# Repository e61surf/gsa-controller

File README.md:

# Surf System Controller - or whatever you want to control...

Feel free to make use of the hardware and software designs here for your project. It is ideally suited for robotics, small electric mobility decives, linear actuator control, or basically anything that needs to drive somewhat high-current motors and needs GPS and Bluetooth. The Atmel 32u4 based, high current board design utilizes:
3 ST Micro motor drivers,
1 Lynx GPS Module, and
1 Microchip BLE Module.

It is designed to fit into a Cinch ModeICE enclosure, which is fully waterproof.

The hardware/software design supports up to a 10 wire, 5 volt control cable and is currently utlizing 2 potentiometers, 3 momentary switches, and 3 LED indicators, but the Atmel 32u4 processor pins can be utlized for many different perposes. 

It can drive up to 3 12v motors/actuators.  Or one of the ST Micro chips can be configured as two 12v outputs for lights, horns, etc...

The board is designed to run on 12v power from a marine or automotive alternator, so it'll handle fluctuations and noise typical in rugged applications.

The BLE module and supporting AVR code supports a custom framed serial protocol for control via a mobile app.  See the documents for more info.

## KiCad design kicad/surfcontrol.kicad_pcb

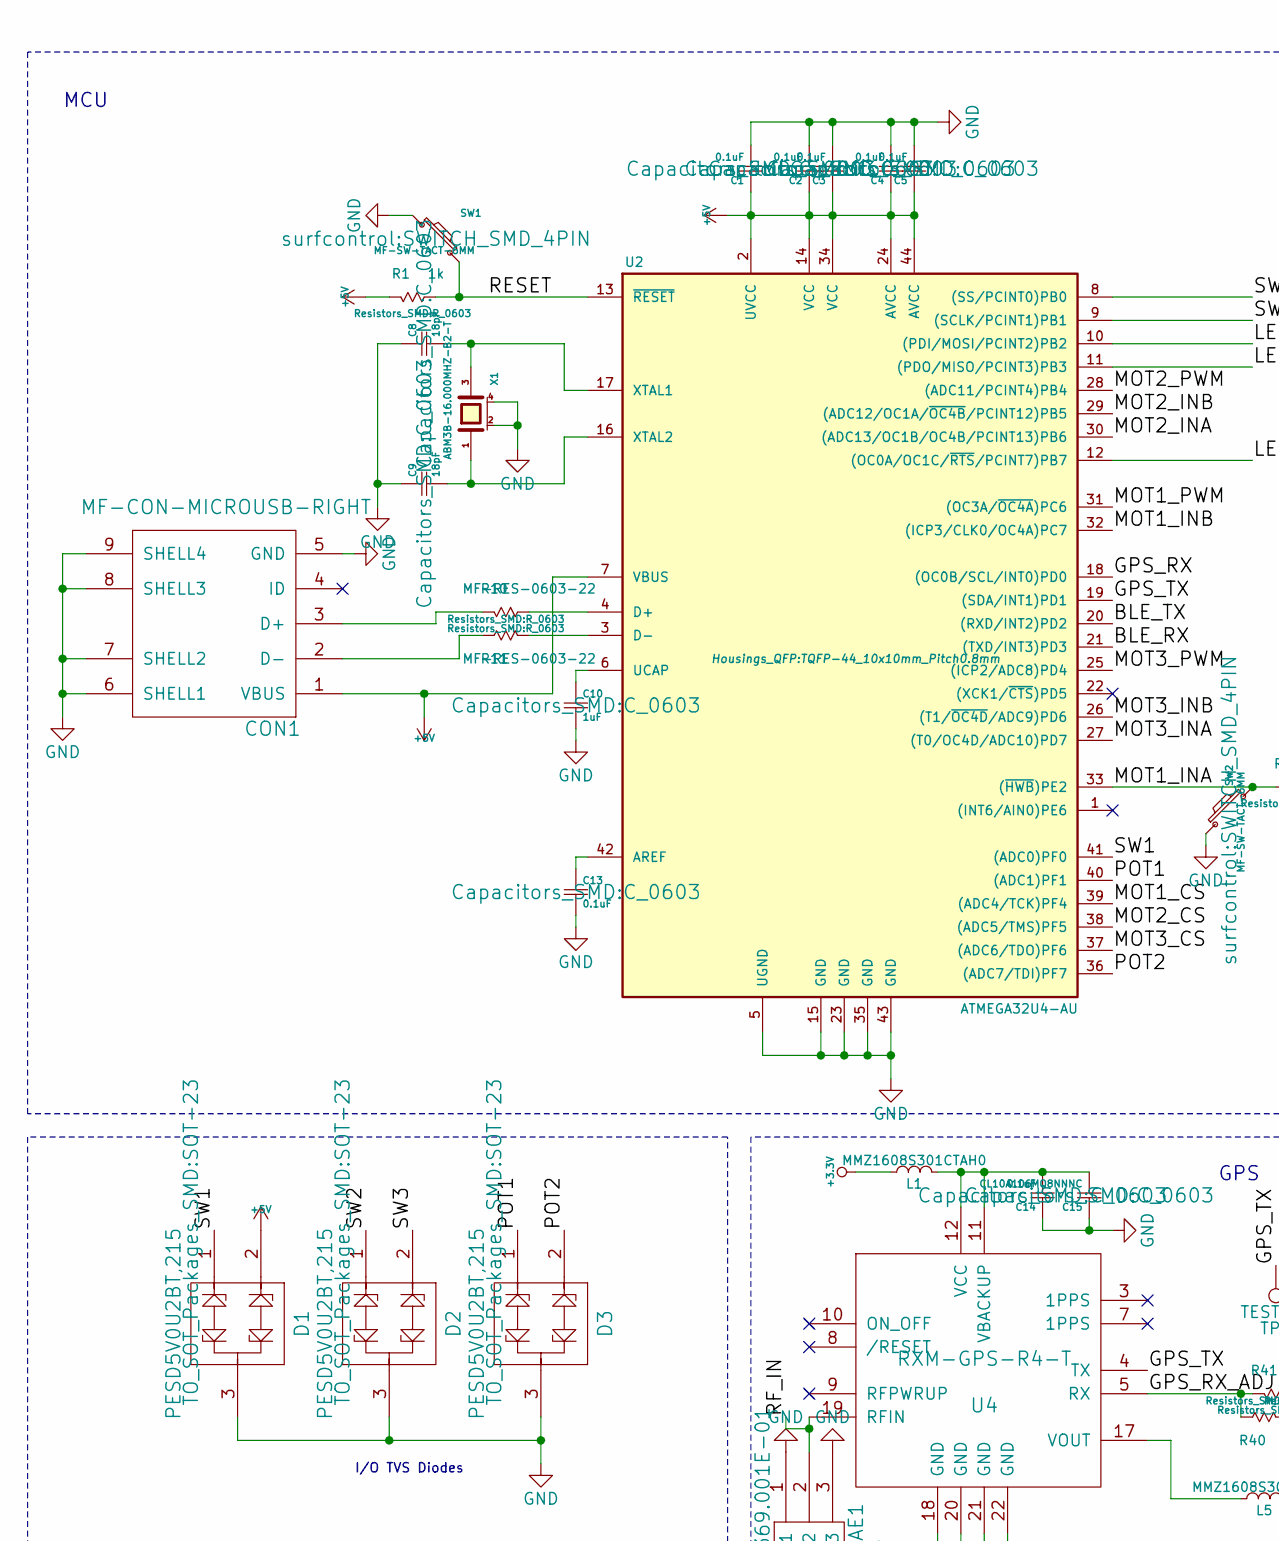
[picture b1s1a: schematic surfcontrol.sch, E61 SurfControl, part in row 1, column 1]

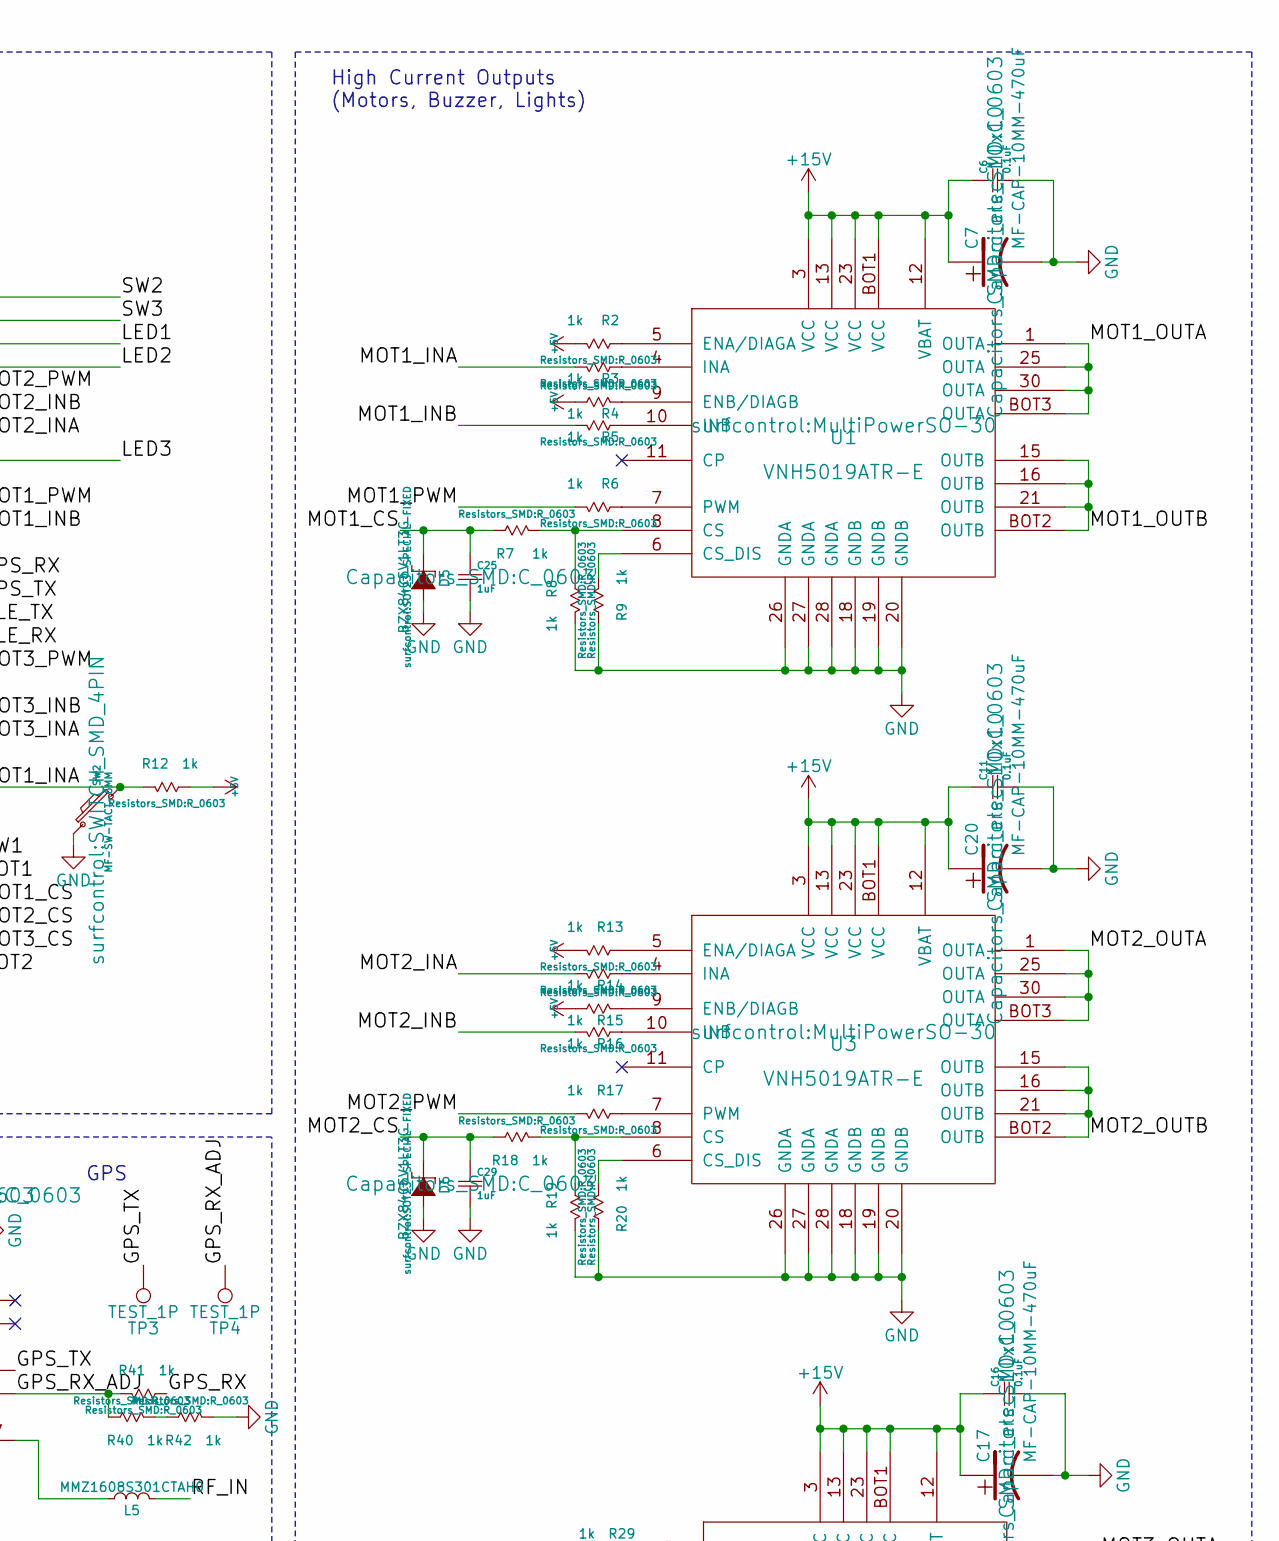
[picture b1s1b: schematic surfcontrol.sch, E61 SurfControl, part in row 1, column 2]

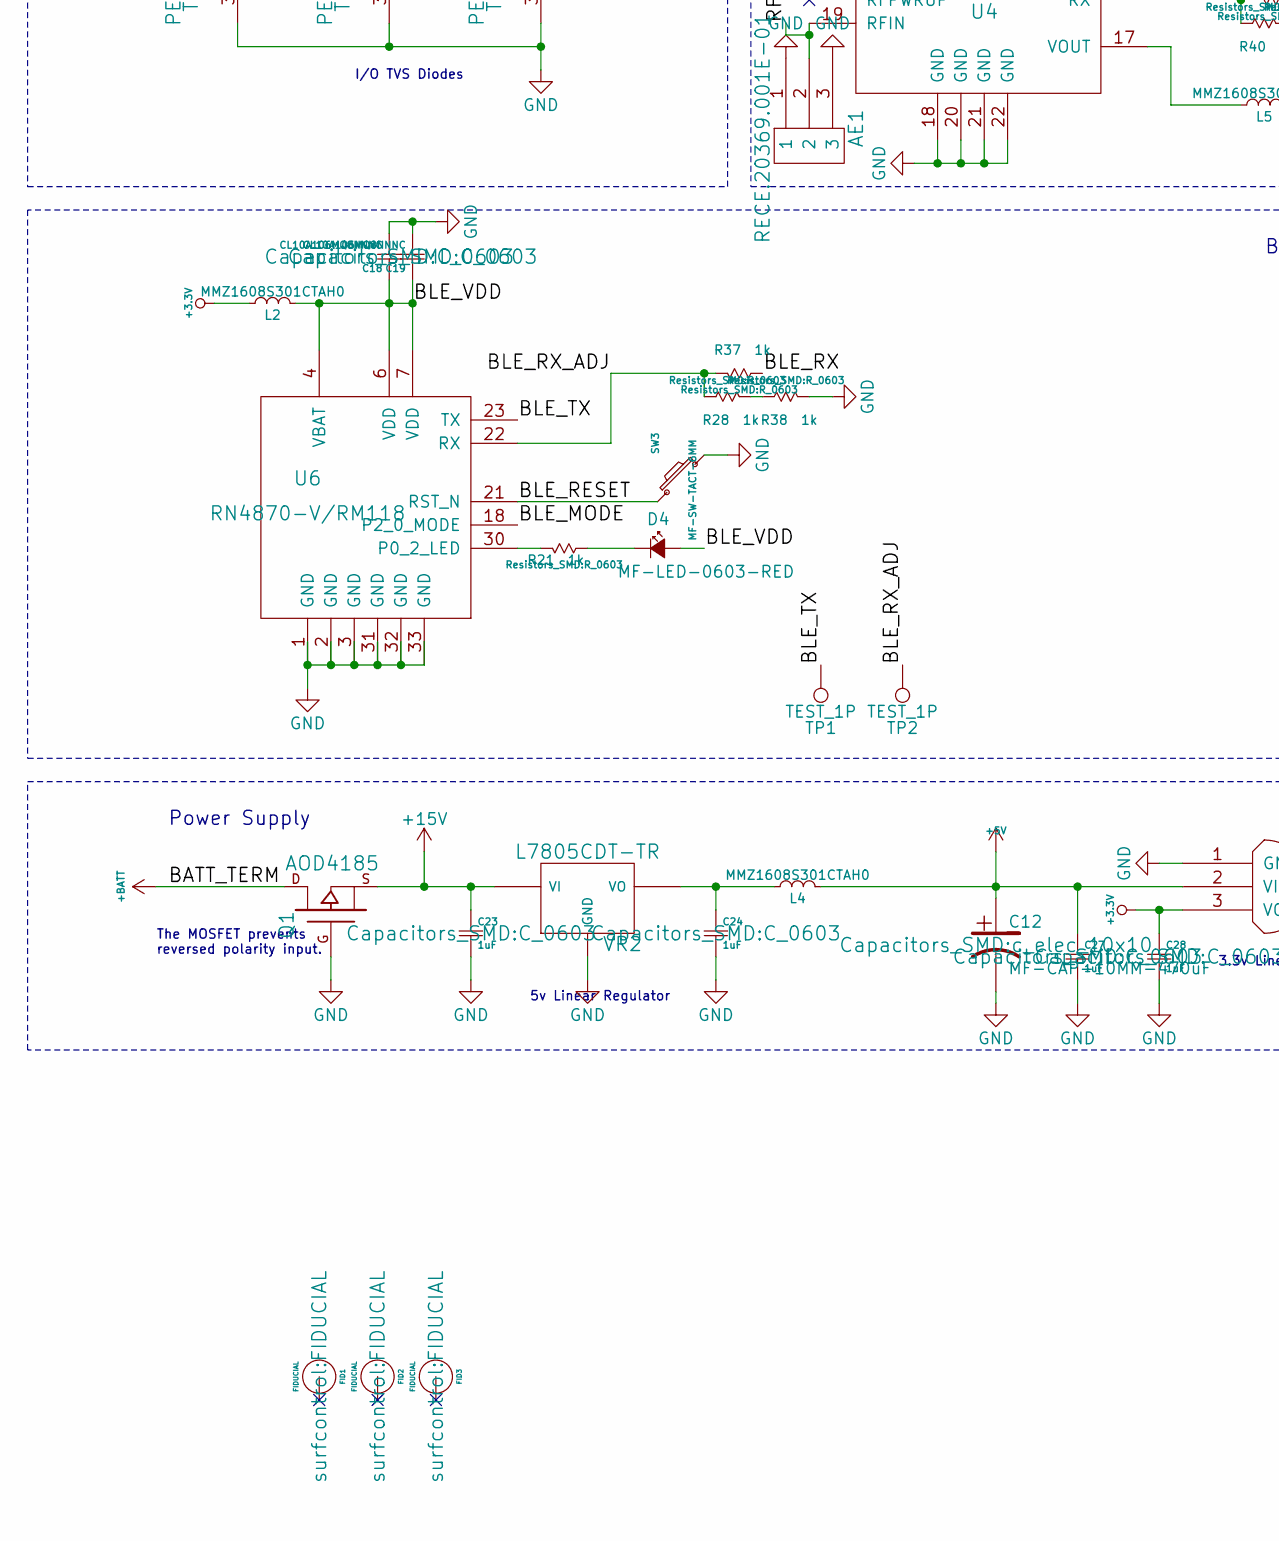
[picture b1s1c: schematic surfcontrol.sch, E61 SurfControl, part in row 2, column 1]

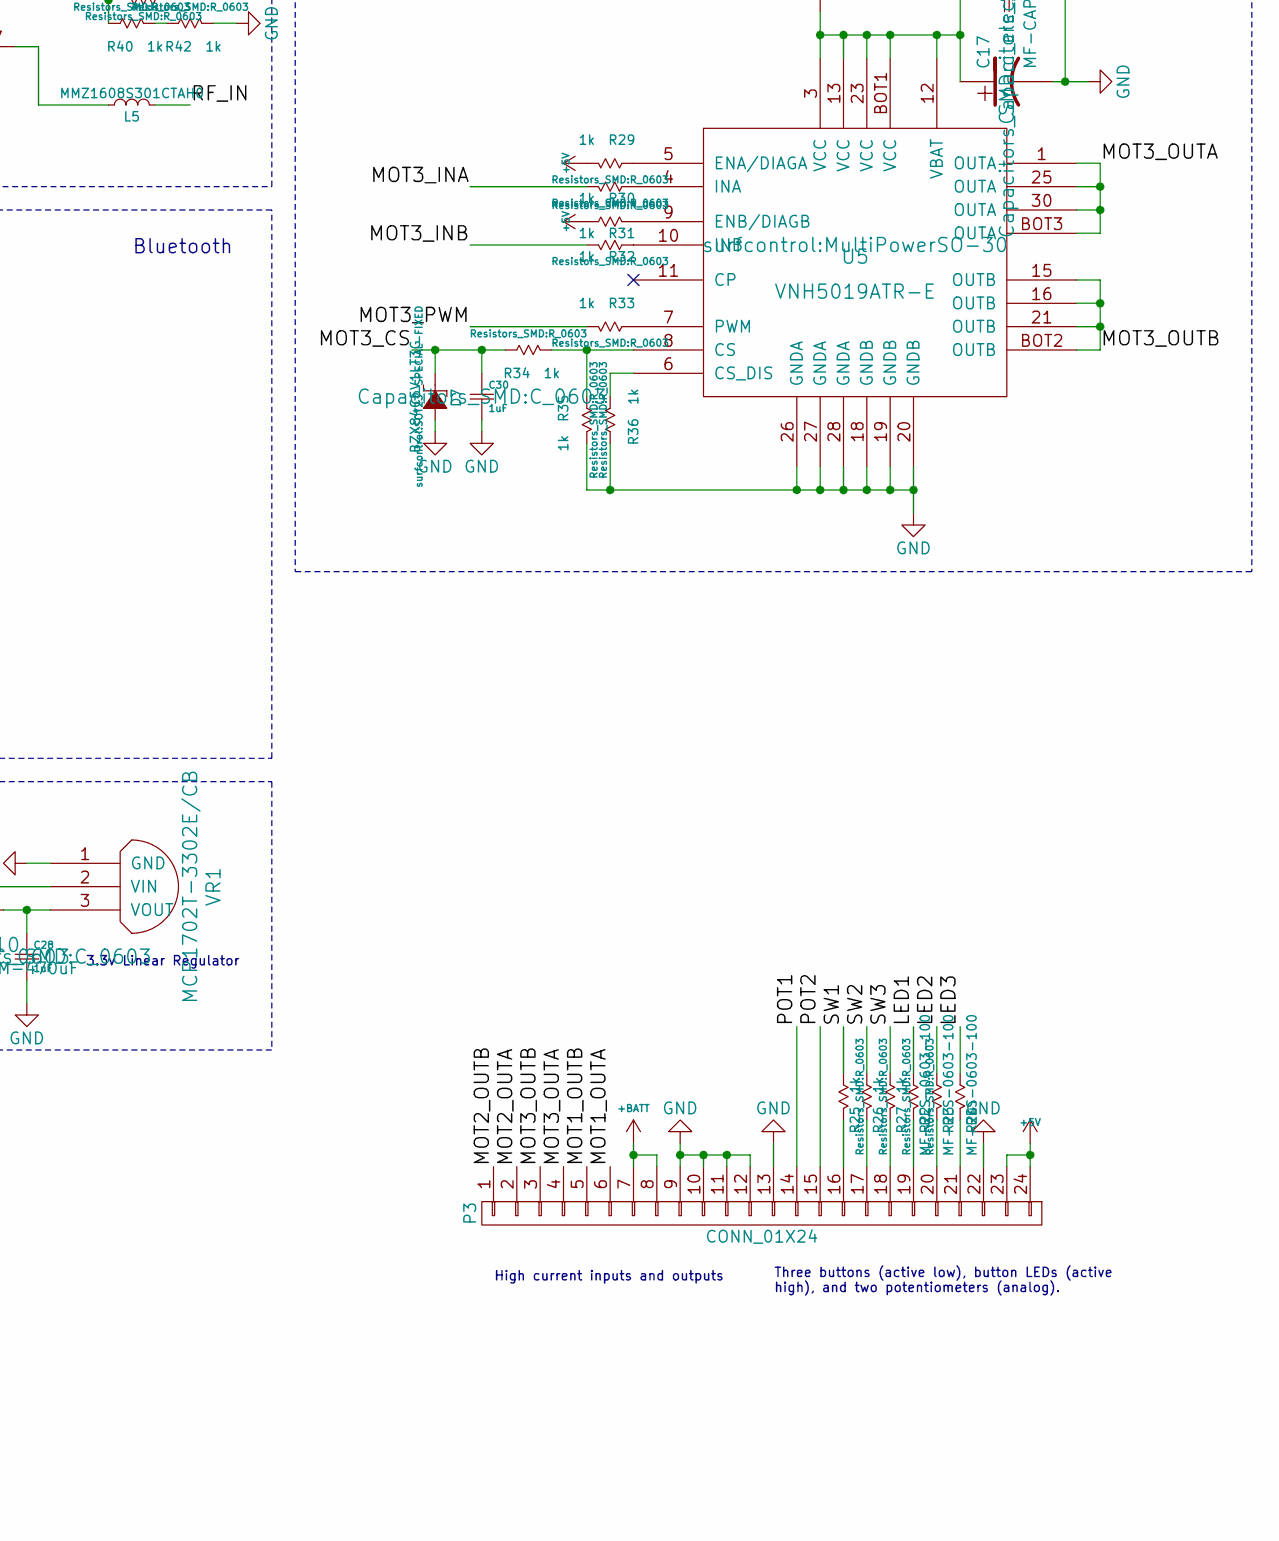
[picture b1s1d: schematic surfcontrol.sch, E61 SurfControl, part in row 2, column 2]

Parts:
AE1: RECE.20369.001E-01; MHF_III; Digikey 931-1157-2-ND
C1, C2, C3, C4, C5, C6, C11, C13, C14, C16: 0.1uF; C_0603; Digikey 1276-1012-1-ND
C7, C12, C17, C20: MF-CAP-10MM-470uF; c_elec_10x10; Digikey Part# 493-6225-2-ND
C8, C9: 18pF; C_0603; Digikey 1276-1089-1-ND
C10, C23, C24, C25, C27, C28, C29, C30: 1uF; C_0603; Digikey 311-1445-1-ND
C15, C18, C19: CL10A106MQ8NNNC; C_0603; Digikey 1276-1119-1-ND
CON1: MF-CON-MICROUSB-RIGHT; USB_Micro-B_SMD; Digikey 151-1206-1-ND
D1, D2, D3: PESD5V0U2BT,215; SOT-23; Digikey 568-4296-1-ND
D4: MF-LED-0603-RED; LED_0603
D5, D6, D7: BZX84C5V1LT3G; SOT23-SPECIAL-FIXED; Digikey BZX84C5V1LT3GOSCT-ND
FID1, FID2, FID3: FIDUCIAL
L1, L2, L4, L5: MMZ1608S301CTAH0; SM0603_VALUE; Digikey 445-172727-1-ND
P3: CONN_01X24; CINCH_MODICE_ME-MX_24POS
Q1: AOD4185; TO-252-2Lead; Digikey 785-1222-1-ND
R1, R2, R3, R4, R5, R6, R7, R8, R9, R12, R13, R14, R15, R16, R17, R18, R19, R20, R21, R25, R26, R27, R28, R29, R30, R31, R32, R33, R34, R35, R36, R37, R38, R40, R41, R42: 1k; R_0603; Digikey RHM1.0KCGCT-ND
R10, R11: MF-RES-0603-22; R_0603; Digikey RHM22CGCT-ND
R22, R23, R24: MF-RES-0603-100; R_0603; Digikey RHM100CGCT-ND
SW1, SW2, SW3: MF-SW-TACT-6MM; SWITCH_SMD_4PIN; Digikey P12961SCT-ND
TP1, TP2, TP3, TP4: TEST_1P; Pin_Header_Straight_1x01
U1, U3, U5: VNH5019ATR-E; MultiPowerSO-30; Digikey 497-13073-1-ND
U2: ATMEGA32U4-AU; TQFP-44_10x10mm_Pitch0.8mm; Digikey Part# ATMEGA32U4-AU-ND
U4: RXM-GPS-R4-T; R4_SERIES_GPS; Digikey RXM-GPS-R4-TCT-ND
U6: RN4870-V/RM118; RN4870
VR1: MCP1702T-3302E/CB; SOT23-SPECIAL-FIXED; Digikey MCP1702T-3302E/CBCT-ND
VR2: L7805CDT-TR; TO-252-2Lead; Digikey Part# 497-7255-1-ND
X1: ABM3B-16.000MHZ-B2-T; crystal_smd_5x3.2; Digikey 535-9122-1-ND

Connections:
+3.3V: C28.1, L1.1, L2.1, VR1.3 (VOUT)
+5V: C1.1, C2.1, C3.1, C4.1, C5.1, C12.1, C27.1, CON1.1 (VBUS), D1.2, L4.2, P3.23, P3.24, R1.2, R2.1, R4.1, R12.1, R13.1, R15.1, R29.1, R31.1, U2.2 (UVCC), U2.7 (VBUS), U2.14 (VCC), U2.24 (AVCC), U2.34 (VCC), U2.44 (AVCC), VR1.2 (VIN)
+15V: C6.1, C7.1, C11.1, C16.1, C17.1, C20.1, C23.1, Q1.S, U1.3 (VCC), U1.12 (VBAT), U1.13 (VCC), U1.23 (VCC), U1.BOT1 (VCC), U3.3 (VCC), U3.12 (VBAT), U3.13 (VCC), U3.23 (VCC), U3.BOT1 (VCC), U5.3 (VCC), U5.12 (VBAT), U5.13 (VCC), U5.23 (VCC), U5.BOT1 (VCC), VR2.VI
+BATT: P3.7, P3.8, Q1.D
/BLE_MODE: U6.18 (P2_0_MODE)
/BLE_RESET: SW3.1, U6.21 (RST_N)
/BLE_RX: R37.1, U2.21 ((TXD/INT3)PD3)
/BLE_RX_ADJ: R28.2, R37.2, TP2.1, U6.22 (RX)
/BLE_TX: TP1.1, U2.20 ((RXD/INT2)PD2), U6.23 (TX)
/BLE_VDD: C18.1, C19.1, D4.2 (A), L2.2, U6.4 (VBAT), U6.6 (VDD), U6.7 (VDD)
/GPS_RX: R41.1, U2.18 ((OC0B/SCL/INT0)PD0)
/GPS_RX_ADJ: R40.2, R41.2, TP4.1, U4.5 (RX)
/GPS_TX: TP3.1, U2.19 ((SDA/INT1)PD1), U4.4 (TX)
/LED1: R22.1, U2.10 ((PDI/MOSI/PCINT2)PB2)
/LED2: R23.1, U2.11 ((PDO/MISO/PCINT3)PB3)
/LED3: R24.1, U2.12 ((OC0A/OC1C/~RTS~/PCINT7)PB7)
/MOT1_CS: C25.1, D5.2 (K), R7.2, U2.39 ((ADC4/TCK)PF4)
/MOT1_INA: R3.1, R12.2, SW2.2, U2.33 ((~HWB~)PE2)
/MOT1_INB: R5.1, U2.32 ((ICP3/CLK0/OC4A)PC7)
/MOT1_OUTA: P3.6, U1.1 (OUTA), U1.25 (OUTA), U1.30 (OUTA), U1.BOT3 (OUTA)
/MOT1_OUTB: P3.5, U1.15 (OUTB), U1.16 (OUTB), U1.21 (OUTB), U1.BOT2 (OUTB)
/MOT1_PWM: R6.1, U2.31 ((OC3A/~OC4A~)PC6)
/MOT2_CS: C29.1, D6.2 (K), R18.2, U2.38 ((ADC5/TMS)PF5)
/MOT2_INA: R14.1, U2.30 ((ADC13/OC1B/OC4B/PCINT13)PB6)
/MOT2_INB: R16.1, U2.29 ((ADC12/OC1A/~OC4B~/PCINT12)PB5)
/MOT2_OUTA: P3.2, U3.1 (OUTA), U3.25 (OUTA), U3.30 (OUTA), U3.BOT3 (OUTA)
/MOT2_OUTB: P3.1, U3.15 (OUTB), U3.16 (OUTB), U3.21 (OUTB), U3.BOT2 (OUTB)
/MOT2_PWM: R17.1, U2.28 ((ADC11/PCINT4)PB4)
/MOT3_CS: C30.1, D7.2 (K), R34.2, U2.37 ((ADC6/TDO)PF6)
/MOT3_INA: R30.1, U2.27 ((T0/OC4D/ADC10)PD7)
/MOT3_INB: R32.1, U2.26 ((T1/~OC4D~/ADC9)PD6)
/MOT3_OUTA: P3.4, U5.1 (OUTA), U5.25 (OUTA), U5.30 (OUTA), U5.BOT3 (OUTA)
/MOT3_OUTB: P3.3, U5.15 (OUTB), U5.16 (OUTB), U5.21 (OUTB), U5.BOT2 (OUTB)
/MOT3_PWM: R33.1, U2.25 ((ICP2/ADC8)PD4)
/POT1: D3.1, P3.14, U2.40 ((ADC1)PF1)
/POT2: D3.2, P3.15, U2.36 ((ADC7/TDI)PF7)
/RESET: R1.1, SW1.2, U2.13 (~RESET~)
/RF_IN: AE1.2, L5.1, U4.19 (RFIN)
/SW1: D1.1, R25.1, U2.41 ((ADC0)PF0)
/SW2: D2.1, R26.1, U2.8 ((SS/PCINT0)PB0)
/SW3: D2.2, R27.1, U2.9 ((SCLK/PCINT1)PB1)
GND: AE1.1, AE1.3, C1.2, C2.2, C3.2, C4.2, C5.2, C6.2, C7.2, C8.1, C9.1, C10.2, C11.2, C12.2, C13.2, C14.1, C15.1, C16.2, C17.2, C18.2, C19.2, C20.2, C23.2, C24.2, C25.2, C27.2, C28.2, C29.2, C30.2, CON1.5 (GND), CON1.6 (SHELL1), CON1.7 (SHELL2), CON1.8 (SHELL3), CON1.9 (SHELL4), D1.3, D2.3, D3.3, D5.1 (A), D6.1 (A), D7.1 (A), P3.9, P3.10, P3.11, P3.12, P3.13, P3.22, Q1.G, R8.1, R9.2, R19.1, R20.2, R35.1, R36.2, R38.1, R42.1, SW1.1, SW2.1, SW3.2, U1.18 (GNDB), U1.19 (GNDB), U1.20 (GNDB), U1.26 (GNDA), U1.27 (GNDA), U1.28 (GNDA), U2.5 (UGND), U2.15 (GND), U2.23 (GND), U2.35 (GND), U2.43 (GND), U3.18 (GNDB), U3.19 (GNDB), U3.20 (GNDB), U3.26 (GNDA), U3.27 (GNDA), U3.28 (GNDA), U4.18 (GND), U4.20 (GND), U4.21 (GND), U4.22 (GND), U5.18 (GNDB), U5.19 (GNDB), U5.20 (GNDB), U5.26 (GNDA), U5.27 (GNDA), U5.28 (GNDA), U6.1 (GND), U6.2 (GND), U6.3 (GND), U6.31 (GND), U6.32 (GND), U6.33 (GND), VR1.1 (GND), VR2.GND, X1.2, X1.4
unnamed: C8.2, U2.17 (XTAL1), X1.3
unnamed: C9.2, U2.16 (XTAL2), X1.1
unnamed: C10.1, U2.6 (UCAP)
unnamed: C13.1, U2.42 (AREF)
unnamed: C14.2, C15.2, L1.2, U4.11 (VBACKUP), U4.12 (VCC)
unnamed: C24.1, L4.1, VR2.VO
unnamed: CON1.2 (D-), R11.2
unnamed: CON1.3 (D+), R10.2
unnamed: D4.1 (K), R21.1
unnamed: L5.2, U4.17 (VOUT)
unnamed: P3.16, R25.2
unnamed: P3.17, R26.2
unnamed: P3.18, R27.2
unnamed: P3.19, R22.2
unnamed: P3.20, R23.2
unnamed: P3.21, R24.2
unnamed: R2.2, U1.5 (ENA/DIAGA)
unnamed: R3.2, U1.4 (INA)
unnamed: R4.2, U1.9 (ENB/DIAGB)
unnamed: R5.2, U1.10 (INB)
unnamed: R6.2, U1.7 (PWM)
unnamed: R7.1, R8.2, U1.8 (CS)
unnamed: R9.1, U1.6 (CS_DIS)
unnamed: R10.1, U2.4 (D+)
unnamed: R11.1, U2.3 (D-)
unnamed: R13.2, U3.5 (ENA/DIAGA)
unnamed: R14.2, U3.4 (INA)
unnamed: R15.2, U3.9 (ENB/DIAGB)
unnamed: R16.2, U3.10 (INB)
unnamed: R17.2, U3.7 (PWM)
unnamed: R18.1, R19.2, U3.8 (CS)
unnamed: R20.1, U3.6 (CS_DIS)
unnamed: R21.2, U6.30 (P0_2_LED)
unnamed: R28.1, R38.2
unnamed: R29.2, U5.5 (ENA/DIAGA)
unnamed: R30.2, U5.4 (INA)
unnamed: R31.2, U5.9 (ENB/DIAGB)
unnamed: R32.2, U5.10 (INB)
unnamed: R33.2, U5.7 (PWM)
unnamed: R34.1, R35.2, U5.8 (CS)
unnamed: R36.1, U5.6 (CS_DIS)
unnamed: R40.1, R42.2

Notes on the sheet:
Power Supply
Three buttons (active low), button LEDs (active high), and two potentiometers (analog).
The MOSFET prevents reversed polarity input.
I/O TVS Diodes
5v Linear Regulator
3.3v Linear Regulator
High Current Outputs (Motors, Buzzer, Lights)
GPS
MCU
Bluetooth
High current inputs and outputs

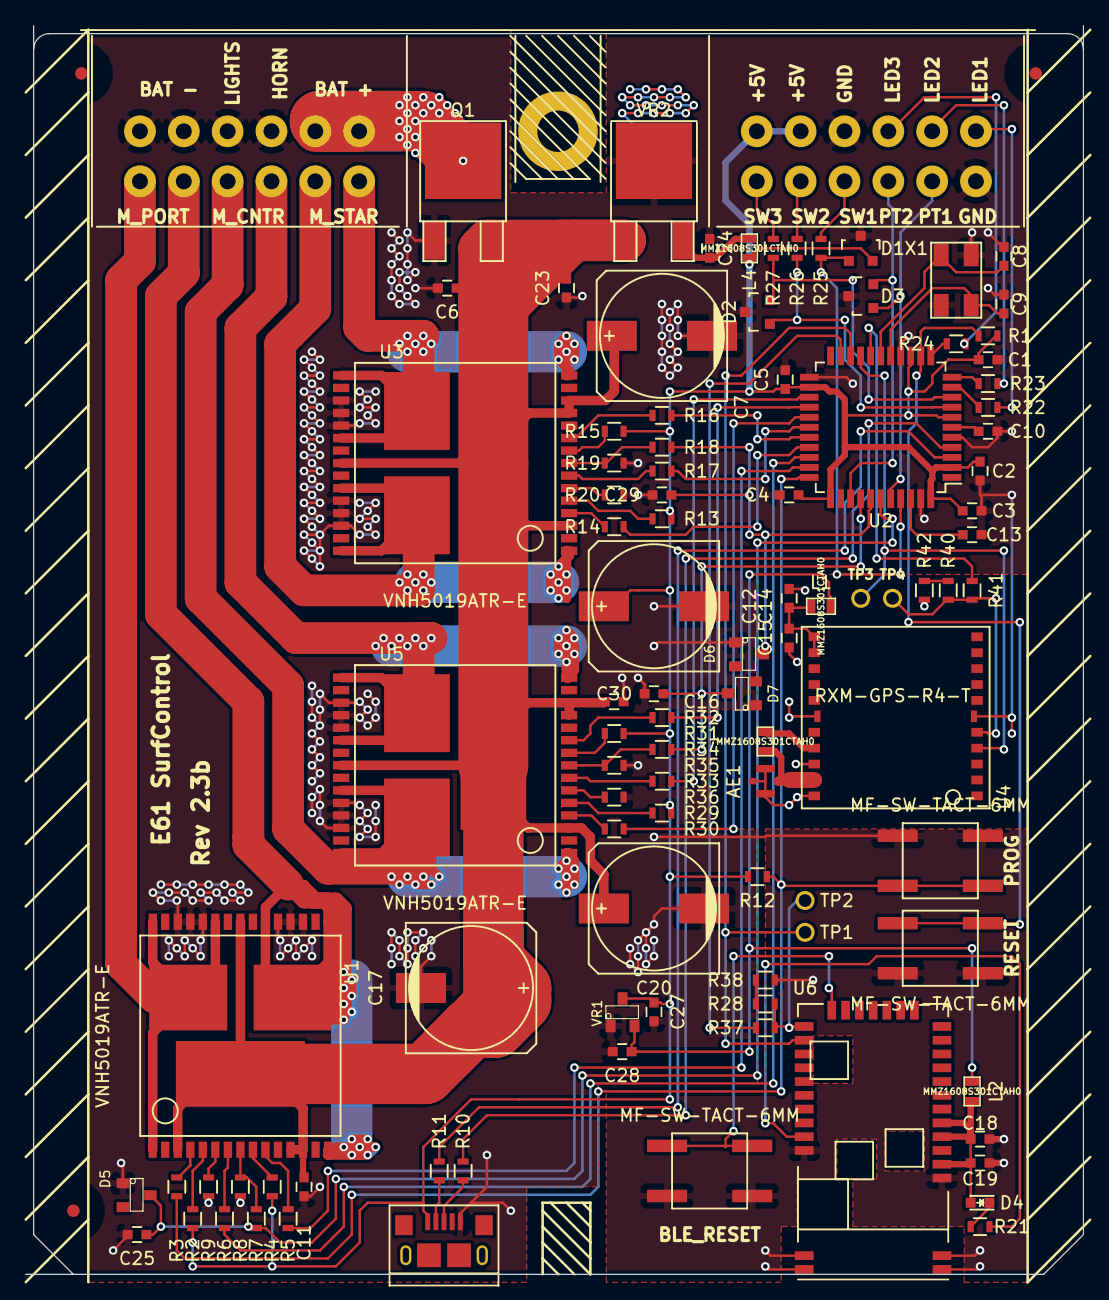
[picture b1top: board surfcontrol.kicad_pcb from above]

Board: 2 copper layers, 84.5 x 99.7 mm, 102 parts (0 on the bottom side), 83 nets.

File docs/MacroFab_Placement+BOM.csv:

###,Module,positions,-,created,on,Sat,13,Jun,2015,02:13:41,PM,MDT,###
###,Printed,by,Pcbnew,version,pcbnew,(22-Jun-2014,BZR,4027)-stable,,,,,
##,Unit,=,inches,Angle,=,deg.,,,,,,,
##,Side,:,F.Cu,,,,,,,,,,
Ref,Val,Package,PosX,PosY,Rot,Side,Digikey Part#,MacroFab Part#,,,,,
AE1,ANTENNA,U.FL_SMT_ANTENNA,1.9,3.825,90,F.Cu,H9161CT-ND,,,,,,
AE2,ANTENNA,SPLATCH_ANTENNA,0.75,1.075,180,F.Cu,ANT-418-SP-ND,,,,,,
C1,0.1uF,SM0603,1.525,2.175,270,F.Cu,1276-1012-1-ND,MF-CAP-0603-0.1uF,,,,,
C2,0.1uF,SM0603,1.25,2.675,180,F.Cu,1276-1012-1-ND,MF-CAP-0603-0.1uF,,,,,
C3,0.1uF,SM0603,1.425,2.85,90,F.Cu,1276-1012-1-ND,MF-CAP-0603-0.1uF,,,,,
C4,0.1uF,SM0603,1.875,2.85,90,F.Cu,1276-1012-1-ND,MF-CAP-0603-0.1uF,,,,,
C5,0.1uF,SM0603,2,2.375,270,F.Cu,1276-1012-1-ND,MF-CAP-0603-0.1uF,,,,,
C6,0.1uF,SM0603,4.05,3,0,F.Cu,1276-1012-1-ND,MF-CAP-0603-0.1uF,,,,,
C7,470uF,c_elec_10x10,3.1,3,0,F.Cu,493-6225-2-ND,MF-CAP-10MM-470uF,,,,,
C8,18pF,SM0603,1.8,1.85,0,F.Cu,1276-1089-1-ND,MF-CAP-0603-18pF,,,,,
C9,18pF,SM0603,1.65,1.85,180,F.Cu,1276-1089-1-ND,MF-CAP-0603-18pF,,,,,
C10,1uF,SM0603,1.25,2.55,180,F.Cu,311-1445-1-ND,MF-CAP-0603-1uF,,,,,
C11,0.1uF,SM0603,4.05,2.1,0,F.Cu,1276-1012-1-ND,MF-CAP-0603-0.1uF,,,,,
C12,470uF,c_elec_10x10,3.1,2.1,0,F.Cu,493-6225-2-ND,MF-CAP-10MM-470uF,,,,,
C13,0.1uF,SM0603,1.55,2.975,90,F.Cu,1276-1012-1-ND,MF-CAP-0603-0.1uF,,,,,
C14,0.1uF,SM0603,1.875,3.425,180,F.Cu,1276-1012-1-ND,MF-CAP-0603-0.1uF,,,,,
C15,10uF,SM0603,1.875,3.5,180,F.Cu,1276-1119-1-ND,,,,,,
C16,0.1uF,SM0603,4.05,1.2,0,F.Cu,1276-1012-1-ND,MF-CAP-0603-0.1uF,,,,,
C17,470uF,c_elec_10x10,3.1,1.2,0,F.Cu,493-6225-2-ND,MF-CAP-10MM-470uF,,,,,
C18,0.1uF,SM0603,2.7,0.825,180,F.Cu,1276-1012-1-ND,MF-CAP-0603-0.1uF,,,,,
C19,0.1uF,SM0603,2.7,0.75,180,F.Cu,1276-1012-1-ND,MF-CAP-0603-0.1uF,,,,,
C20,10uF,SM0603,2.7,0.675,180,F.Cu,1276-1119-1-ND,,,,,,
C21,0.1uF,SM0603,1.8,0.425,0,F.Cu,1276-1012-1-ND,MF-CAP-0603-0.1uF,,,,,
C22,10uF,SM0603,1.8,0.35,0,F.Cu,1276-1119-1-ND,,,,,,
C23,1uF,SM0603,3.55,1,180,F.Cu,311-1445-1-ND,MF-CAP-0603-1uF,,,,,
C24,1uF,SM0603,3.2,0.925,270,F.Cu,311-1445-1-ND,MF-CAP-0603-1uF,,,,,
C25,1uF,SM0603,2.45,3.1,90,F.Cu,311-1445-1-ND,MF-CAP-0603-1uF,,,,,
C26,470uF,c_elec_10x10,3.1,0.425,0,F.Cu,493-6225-2-ND,MF-CAP-10MM-470uF,,,,,
C27,1uF,SM0603,3.05,0.925,90,F.Cu,311-1445-1-ND,MF-CAP-0603-1uF,,,,,
C28,1uF,SM0603,3.05,0.8,90,F.Cu,311-1445-1-ND,MF-CAP-0603-1uF,,,,,
C29,1uF,SM0603,2.375,3.1,90,F.Cu,311-1445-1-ND,MF-CAP-0603-1uF,,,,,
C30,1uF,SM0603,2.3,3.1,90,F.Cu,311-1445-1-ND,MF-CAP-0603-1uF,,,,,
CON1,USB-MINI-B,USB_MINI_B_fixed,0.35,3.15,0,F.Cu,151-1206-1-ND,,,,,,
D1,PESD5V0U2BT,SOT23,0.6,1.5,180,F.Cu,568-4296-1-ND,,,,,,
D2,PESD5V0U2BT,SOT23,0.75,1.5,180,F.Cu,568-4296-1-ND,,,,,,
D3,PESD5V0U2BT,SOT23,0.9,1.5,180,F.Cu,568-4296-1-ND,,,,,,
D4,LEARN,SMDLED-0603,2.575,0.6,270,F.Cu,160-1447-1-ND,MF-LED-0603-RED,,,,,
D5,5.1v,SOT23-SPECIAL,2.6,2.85,0,F.Cu,BZX84C5V1LT3GOSCT-ND,,,,,,
D6,5.1v,SOT23-SPECIAL,2.45,2.85,0,F.Cu,BZX84C5V1LT3GOSCT-ND,,,,,,
D7,5.1v,SOT23-SPECIAL,2.3,2.85,0,F.Cu,BZX84C5V1LT3GOSCT-ND,,,,,,
FID1,FIDUCIAL,FIDUCIAL,0.55,3.85,0,F.Cu,,,,,,,
FID2,FIDUCIAL,FIDUCIAL,4.15,0.35,0,F.Cu,,,,,,,
FID3,FIDUCIAL,FIDUCIAL,0.55,0.35,0,F.Cu,,,,,,,
JP1,JUMPER_SMALL,SMD_JUMPER,3.625,3.825,0,F.Cu,952-1474-6-ND,,,,,,
JP2,JUMPER_SMALL,SMD_JUMPER,3.625,3.075,0,F.Cu,952-1474-6-ND,,,,,,
JP3,JUMPER_SMALL,SMD_JUMPER,3.625,2.025,0,F.Cu,952-1474-6-ND,,,,,,
JP4,JUMPER_SMALL,SMD_JUMPER,3.625,1.275,0,F.Cu,952-1474-6-ND,,,,,,
JP5,JUMPER_SMALL,SMD_JUMPER,3.625,2.925,0,F.Cu,952-1474-6-ND,,,,,,
JP6,JUMPER_SMALL,SMD_JUMPER,3.625,2.175,0,F.Cu,952-1474-6-ND,,,,,,
K3,SWITCHES_AND_LED,MOLEX_10,0.3,1.9,90,F.Cu,WM10187-ND,,,,,,
L1,FERRITE_BEAD,SM0603,1.875,3.35,180,F.Cu,445-172727-1-ND,,,,,,
L2,FERRITE_BEAD,SM0603,2.675,1,270,F.Cu,445-172727-1-ND,,,,,,
L3,FERRITE_BEAD,SM0603,1.925,0.35,180,F.Cu,445-172727-1-ND,,,,,,
L4,FERRITE_BEAD,SM0603,3.125,0.925,270,F.Cu,445-172727-1-ND,,,,,,
L5,FERRITE_BEAD,SM0603,2.025,3.625,180,F.Cu,445-172727-1-ND,,,,,,
Q1,MOSFET_P,DPAK2,3.925,0.875,180,F.Cu,785-1222-1-ND,,,,,,
R1,1k,SM0603,1.15,1.625,270,F.Cu,RHM1.0KCGCT-ND,MF-RES-0603-1K,,,,,
R2,1k,SM0603,3.1,3.575,0,F.Cu,RHM1.0KCGCT-ND,MF-RES-0603-1K,,,,,
R3,1k,SM0603,3.225,3.625,0,F.Cu,RHM1.0KCGCT-ND,MF-RES-0603-1K,,,,,
R4,1k,SM0603,3.225,3.325,0,F.Cu,RHM1.0KCGCT-ND,MF-RES-0603-1K,,,,,
R5,1k,SM0603,3.1,3.275,0,F.Cu,RHM1.0KCGCT-ND,MF-RES-0603-1K,,,,,
R6,1k,SM0603,3.1,3.475,0,F.Cu,RHM1.0KCGCT-ND,MF-RES-0603-1K,,,,,
R7,1k,SM0603,3.1,3.375,180,F.Cu,RHM1.0KCGCT-ND,MF-RES-0603-1K,,,,,
R8,1k,SM0603,3.225,3.425,0,F.Cu,RHM1.0KCGCT-ND,MF-RES-0603-1K,,,,,
R9,1k,SM0603,3.225,3.525,180,F.Cu,RHM1.0KCGCT-ND,MF-RES-0603-1K,,,,,
R10,22,SM0603,0.675,3.125,180,F.Cu,RHM22CGCT-ND,MF-RES-0603-22,,,,,
R11,22,SM0603,0.675,3.2,180,F.Cu,RHM22CGCT-ND,MF-RES-0603-22,,,,,
R12,1k,SM0603,2.175,1.625,90,F.Cu,RHM1.0KCGCT-ND,MF-RES-0603-1K,,,,,
R13,1k,SM0603,3.1,1.775,0,F.Cu,RHM1.0KCGCT-ND,MF-RES-0603-1K,,,,,
R14,1k,SM0603,3.225,1.825,0,F.Cu,RHM1.0KCGCT-ND,MF-RES-0603-1K,,,,,
R15,1k,SM0603,3.225,1.525,0,F.Cu,RHM1.0KCGCT-ND,MF-RES-0603-1K,,,,,
R16,1k,SM0603,3.1,1.475,0,F.Cu,RHM1.0KCGCT-ND,MF-RES-0603-1K,,,,,
R17,1k,SM0603,3.1,1.675,0,F.Cu,RHM1.0KCGCT-ND,MF-RES-0603-1K,,,,,
R18,1k,SM0603,3.1,1.575,180,F.Cu,RHM1.0KCGCT-ND,MF-RES-0603-1K,,,,,
R19,1k,SM0603,3.225,1.625,0,F.Cu,RHM1.0KCGCT-ND,MF-RES-0603-1K,,,,,
R20,1k,SM0603,3.225,1.725,180,F.Cu,RHM1.0KCGCT-ND,MF-RES-0603-1K,,,,,
R22,100,SM0603,0.55,1.675,0,F.Cu,RHM100CGCT-ND,MF-RES-0603-100,,,,,
R23,100,SM0603,0.55,1.75,0,F.Cu,RHM100CGCT-ND,MF-RES-0603-100,,,,,
R24,100,SM0603,0.55,1.825,0,F.Cu,RHM100CGCT-ND,MF-RES-0603-100,,,,,
R25,1k,SM0603,0.55,1.9,0,F.Cu,RHM1.0KCGCT-ND,MF-RES-0603-1K,,,,,
R26,1k,SM0603,0.55,1.975,0,F.Cu,RHM1.0KCGCT-ND,MF-RES-0603-1K,,,,,
R27,1k,SM0603,0.55,2.05,0,F.Cu,RHM1.0KCGCT-ND,MF-RES-0603-1K,,,,,
R29,1k,SM0603,3.1,2.675,0,F.Cu,RHM1.0KCGCT-ND,MF-RES-0603-1K,,,,,
R30,1k,SM0603,3.225,2.725,0,F.Cu,RHM1.0KCGCT-ND,MF-RES-0603-1K,,,,,
R31,1k,SM0603,3.225,2.425,0,F.Cu,RHM1.0KCGCT-ND,MF-RES-0603-1K,,,,,
R32,1k,SM0603,3.1,2.375,0,F.Cu,RHM1.0KCGCT-ND,MF-RES-0603-1K,,,,,
R33,1k,SM0603,3.1,2.575,0,F.Cu,RHM1.0KCGCT-ND,MF-RES-0603-1K,,,,,
R34,1k,SM0603,3.1,2.475,180,F.Cu,RHM1.0KCGCT-ND,MF-RES-0603-1K,,,,,
R35,1k,SM0603,3.225,2.525,0,F.Cu,RHM1.0KCGCT-ND,MF-RES-0603-1K,,,,,
R36,1k,SM0603,3.225,2.625,180,F.Cu,RHM1.0KCGCT-ND,MF-RES-0603-1K,,,,,
R37,1k,SM0603,2.375,0.575,0,F.Cu,RHM1.0KCGCT-ND,MF-RES-0603-1K,,,,,
R38,1k,SM0603,2.3,0.3,180,F.Cu,RHM1.0KCGCT-ND,MF-RES-0603-1K,,,,,
R39,100k,SM0603,2.3,0.4,0,F.Cu,RHM100KCGCT-ND,MF-RES-0603-100K,,,,,
R40,1k,SM0603,2.1,2.225,180,F.Cu,RHM1.0KCGCT-ND,MF-RES-0603-1K,,,,,
R41,1k,SM0603,1.9,2.225,0,F.Cu,RHM1.0KCGCT-ND,MF-RES-0603-1K,,,,,
R42,1k,SM0603,2.225,2.225,180,F.Cu,RHM1.0KCGCT-ND,MF-RES-0603-1K,,,,,
SW1,RESET,SWITCH_SMD_4PIN,1.425,1.575,180,F.Cu,P12961SCT-ND,,,,,,
SW2,PROG,SWITCH_SMD_4PIN,1.9,1.575,180,F.Cu,P12961SCT-ND,,,,,,
SW3,LEARN,SWITCH_SMD_4PIN,2.575,0.375,180,F.Cu,P12961SCT-ND,,,,,,
U1,VNH5019,MultiPowerSO-30,3.75,3.45,0,F.Cu,497-13073-1-ND,,,,,,
U2,ATMEGA32U4-A,TQFP44,1.65,2.55,0,F.Cu,ATMEGA32U4-AU-ND,,,,,,
U3,VNH5019,MultiPowerSO-30,3.75,1.65,0,F.Cu,497-13073-1-ND,,,,,,
U4,R4_GPS,R4_SERIES_GPS,1.525,3.625,270,F.Cu,RXM-GPS-R4-TCT-ND,,,,,,
U5,VNH5019,MultiPowerSO-30,3.75,2.55,0,F.Cu,497-13073-1-ND,,,,,,
U6,MS_SERIES_DECODE,SSOP20_FIXED,2.425,0.8,0,F.Cu,LICAL-DEC-MS001-ND,,,,,,
U7,LR_SERIES_RECEIV,LR_SERIES_RECEIV,1.8,0.825,0,F.Cu,RXM-418-LR-ND,,,,,,
VR1,MCP1702,SOT23-SPECIAL,2.9,0.91,270,F.Cu,MCP1702T-3302E/CBCT-ND,,,,,,
VR2,L7805CDT,DPAK2,3.55,0.875,180,F.Cu,497-7255-1-ND,,,,,,
X1,CRYSTAL_SMD_4PIN,crystal_smd_5x3.,1.725,2,90,F.Cu,535-9122-1-ND,,,,,,
##,End,,,,,,,,,,,,

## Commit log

2019-04-10 added code quality badge
2019-04-10 more badges
2025-11-11 Add API documentation for SurfControl firmware
